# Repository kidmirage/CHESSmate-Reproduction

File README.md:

# CHESSmate-Reproduction
The plan is to make a reproduction of the dedicated chess computer CHESSmate released by Commodore in 1978.

CHESSmate was developed by Peter Jennings, author of the KIM-1 MicroChess program, under contract with Commodore International. The CHESSmate’s hardware is based on the venerable KIM-1, but the ROMs are loaded with a custom MicroChess 1.5 image not the KIM’s monitor.

CHESSmate units are extremely hard to find, understandable given that 45 years have passed since they were introduced. My hope is to build a working CHESSmate computer using modern fabrication techniques and components, and to produce a comprehensive set of instructions with modeling files (PCB, 3D Print, etc.) so that anyone else could make one as well.

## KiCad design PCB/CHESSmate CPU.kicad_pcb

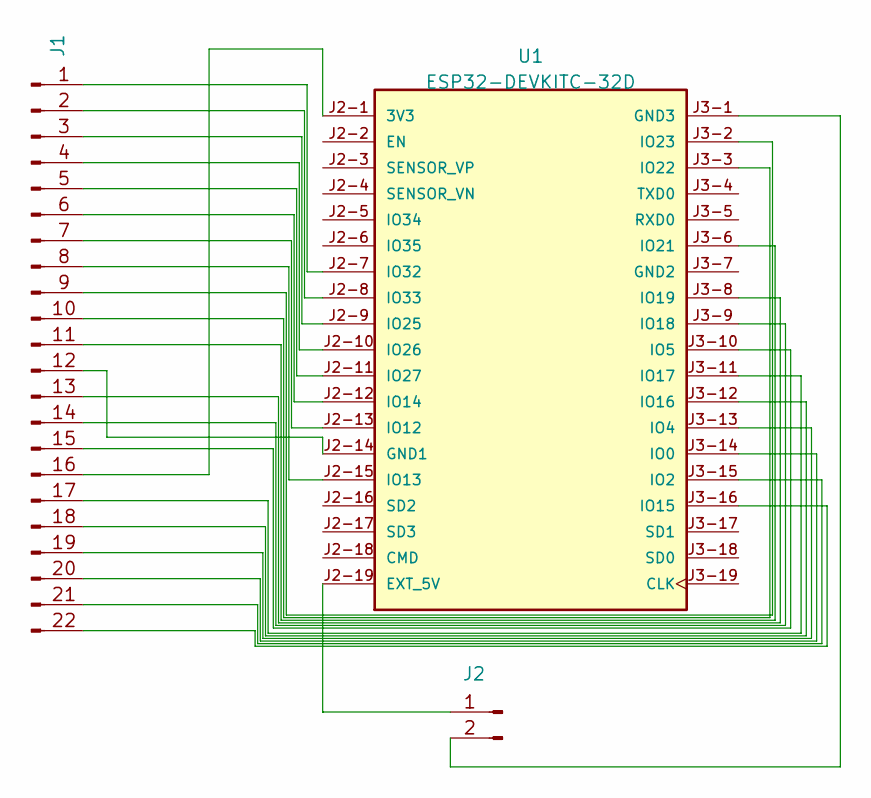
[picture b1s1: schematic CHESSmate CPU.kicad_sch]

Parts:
J1: Conn_01x22_Pin; PinHeader_1x22_P2.54mm_Vertical
J2: Conn_01x02_Pin; PinHeader_1x02_P2.54mm_Vertical
U1: ESP32-DEVKITC-32D; MODULE_ESP32-DEVKITC-32D; PARTREV V4

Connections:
unnamed: J1.1, U1.J2-7 (IO32)
unnamed: J1.2, U1.J2-8 (IO33)
unnamed: J1.3, U1.J2-9 (IO25)
unnamed: J1.4, U1.J2-10 (IO26)
unnamed: J1.5, U1.J2-11 (IO27)
unnamed: J1.6, U1.J2-12 (IO14)
unnamed: J1.7, U1.J2-13 (IO12)
unnamed: J1.8, U1.J2-15 (IO13)
unnamed: J1.9, U1.J3-2 (IO23)
unnamed: J1.10, U1.J3-3 (IO22)
unnamed: J1.11, U1.J3-6 (IO21)
unnamed: J1.12, U1.J2-14 (GND1)
unnamed: J1.13, U1.J3-8 (IO19)
unnamed: J1.14, U1.J3-9 (IO18)
unnamed: J1.15, U1.J3-10 (IO5)
unnamed: J1.16, U1.J2-1 (3V3)
unnamed: J1.17, U1.J3-11 (IO17)
unnamed: J1.18, U1.J3-12 (IO16)
unnamed: J1.19, U1.J3-13 (IO4)
unnamed: J1.20, U1.J3-14 (IO0)
unnamed: J1.21, U1.J3-15 (IO2)
unnamed: J1.22, U1.J3-16 (IO15)
unnamed: J2.1, U1.J2-19 (EXT_5V)
unnamed: J2.2, U1.J3-1 (GND3)

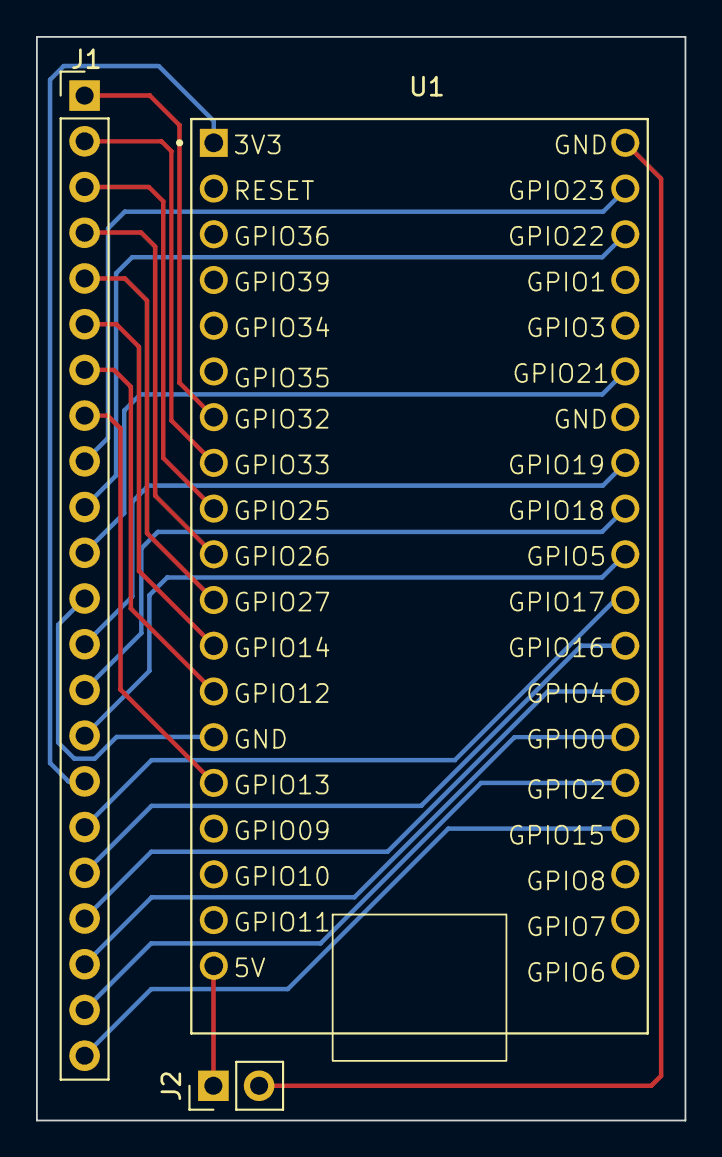
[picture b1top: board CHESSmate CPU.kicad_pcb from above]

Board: 2 copper layers, 36.0 x 60.2 mm, 3 parts (0 on the bottom side), 24 nets.

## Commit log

2024-01-29 Add files via upload
    KiCad files for the latest version of the CHESSmate PCB. Note that the schematic is a little out of date w.r.t. the PCB. Will fix.
2024-01-29 Add files via upload
    KiCad for latest PCB.
2024-01-29 Add files via upload
    Gerber files for producing a CHESSmate PCB.
2024-01-29 Add files via upload
    Arduino Sketch for CHESSmate targeted at an Arduino Pro Mini.
2024-01-31 Add files via upload
    Updated to latest version of schematic.
2024-02-03 Add files via upload
    Working version.
2024-02-05 Add files via upload
    Added CHESSmate code that runs on the ESP32.
2024-02-05 Delete Firmware/CHESSmate.ino
    Moved into CHESSmate folder.
2024-02-05 Delete Firmware/cpu.c
    Moved into CHESSmate folder.
2024-02-13 Add files via upload
    Added daughter board PCB to hold the ESP-32 WROOM.
2024-02-15 Add files via upload
    Got the chess clock, opening book, and random book selection CHESSmate features working in my emulator.
2024-02-15 Create README.md
    Deprecation notice.
2024-02-16 Add files via upload
    Added the Operation Instructions.
2024-02-17 Add files via upload
    Added the Fusion 360 case models.
2024-02-17 Add files via upload
    Added the STEP files too.
2024-02-26 Add files via upload
    Fix for the CHESSmate CPU backpack daughter board.
2024-03-17 Add files via upload
    A second minimal stand.
2024-03-17 Add files via upload
    DXF file used to create membrane mask.
2024-03-17 Rename CM Minimal Stand 2.3mf to CM_Minimal Stand 2.3mf
2024-03-17 Add files via upload
    CPU backpack daughter board.
2024-03-17 Delete Fabrication/CHESSmate_CPU.zip
    Wrong version.
2024-03-17 Rename CHESSmate.zip to CHESSmate PCB.zip
    Rename for consistency.
2024-03-23 Add files via upload
    Added membrane fabrication files.
2024-03-23 Add files via upload
    Switched to printing orientation.
2024-04-17 Add files via upload
    Initial version of a software only emulation of CHESSmate.
2024-04-17 Delete Python/__pycache__ directory
    Cleanup
2024-04-18 Create README.md
    This is a software only CHESSmate emulator written in Python. As far as I know the only dependency is that PyGame must be available. I have tested this on:
    Raspberry Pi 4 - Python 3.11.2 - PyGame 2.1.2
    Windows - Python 3.10.5 - PyGame 2.1.2
2024-04-18 Update README.md
    Added text.
